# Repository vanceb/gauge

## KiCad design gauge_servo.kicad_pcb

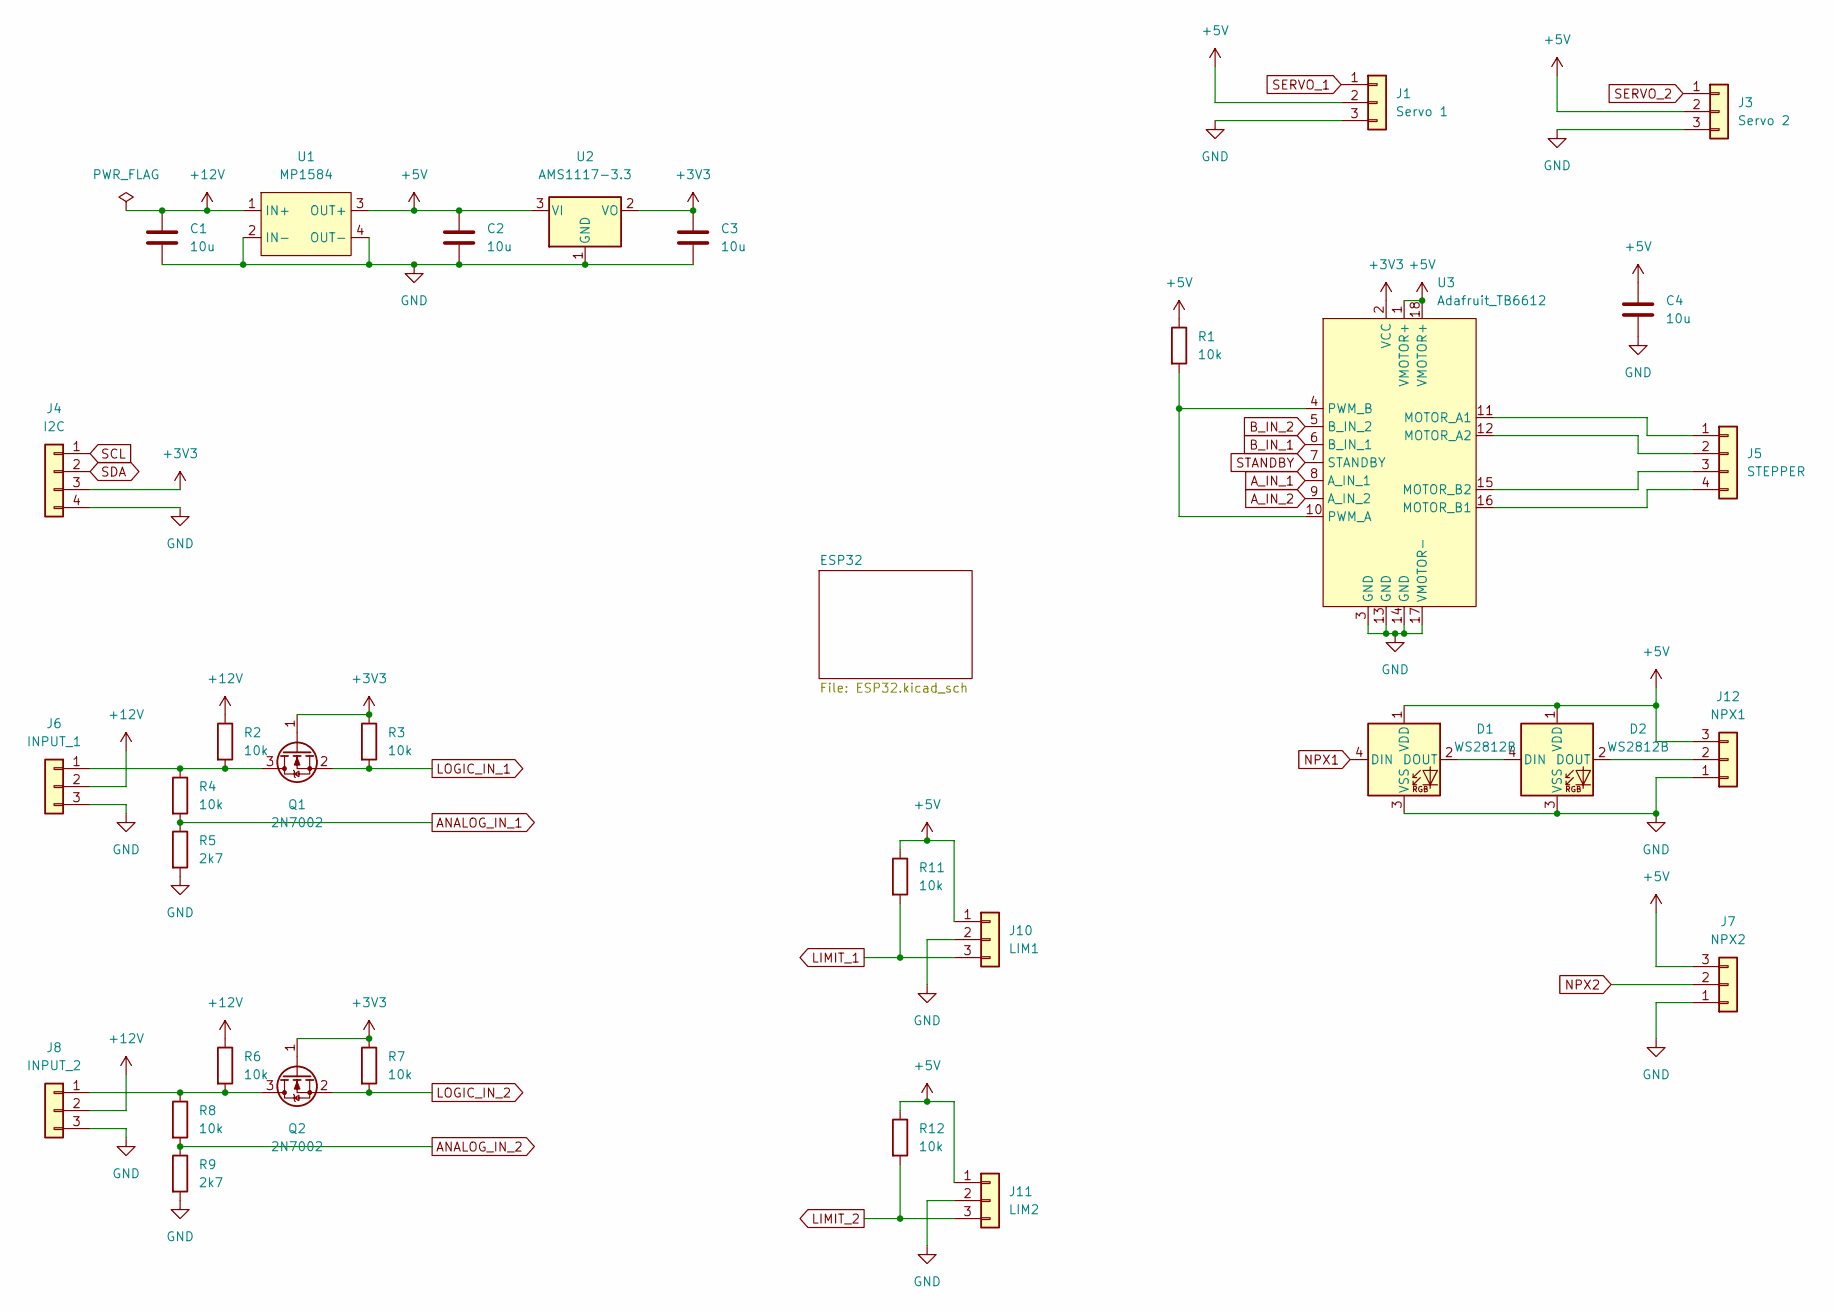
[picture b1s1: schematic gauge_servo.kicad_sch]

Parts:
C1, C2, C3, C4: 10u; C_1206_3216Metric; LCSC C13585
D1, D2: WS2812B; LED_WS2812B_PLCC4_5.0x5.0mm_P3.2mm
J1: Servo 1; PinHeader_1x03_P2.54mm_Vertical
J3: Servo 2; PinHeader_1x03_P2.54mm_Vertical
J4: I2C; PinHeader_1x04_P2.54mm_Vertical
J5: STEPPER; PinHeader_1x04_P2.54mm_Vertical
J6: INPUT_1; PinHeader_1x03_P2.54mm_Vertical
J7: NPX2; PinHeader_1x03_P2.54mm_Vertical
J8: INPUT_2; PinHeader_1x03_P2.54mm_Vertical
J10: LIM1; PinHeader_1x03_P2.54mm_Vertical
J11: LIM2; PinHeader_1x03_P2.54mm_Vertical
J12: NPX1; PinHeader_1x03_P2.54mm_Vertical
Q1, Q2: 2N7002; SOT-23; LCSC C8545
R1, R2, R3, R4, R6, R7, R8, R11, R12: 10k; R_0603_1608Metric; LCSC C25804
R5, R9: 2k7; R_0603_1608Metric; LCSC C13167
U1: MP1584
U2: AMS1117-3.3; SOT-223-3_TabPin2; LCSC C6186
U3: Adafruit_TB6612

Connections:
+3V3: C3.1, J4.3, Q1.1 (G), Q2.1 (G), R3.1, R7.1, U2.2 (VO), U3.2 (VCC); also elsewhere on the board
+5V: C2.1, C4.1, D1.1 (VDD), D2.1 (VDD), J1.2, J3.2, J7.3, J10.1, J11.1, J12.3, R1.1, R11.1, R12.1, U1.3 (OUT+), U2.3 (VI), U3.1 (VMOTOR+), U3.18 (VMOTOR+)
+12V: C1.1, J6.2, J8.2, R2.1, R6.1, U1.1 (IN+)
ANALOG_IN_1: R4.2, R5.1; also elsewhere on the board
ANALOG_IN_2: R8.2, R9.1; also elsewhere on the board
A_IN_1: U3.8 (A_IN_1); also elsewhere on the board
A_IN_2: U3.9 (A_IN_2); also elsewhere on the board
B_IN_1: U3.6 (B_IN_1); also elsewhere on the board
B_IN_2: U3.5 (B_IN_2); also elsewhere on the board
GND: C1.2, C2.2, C3.2, C4.2, D1.3 (VSS), D2.3 (VSS), J1.3, J3.3, J4.4, J6.3, J7.1, J8.3, J10.2, J11.2, J12.1, R5.2, R9.2, U1.2 (IN-), U1.4 (OUT-), U2.1 (GND), U3.3 (GND), U3.13 (GND), U3.14 (GND), U3.17 (VMOTOR-); also elsewhere on the board
LIMIT_1: J10.3, R11.2; also elsewhere on the board
LIMIT_2: J11.3, R12.2; also elsewhere on the board
LOGIC_IN_1: Q1.2 (S), R3.2; also elsewhere on the board
LOGIC_IN_2: Q2.2 (S), R7.2; also elsewhere on the board
NPX1: D1.4 (DIN); also elsewhere on the board
NPX2: J7.2; also elsewhere on the board
unnamed: D1.2 (DOUT), D2.4 (DIN)
unnamed: D2.2 (DOUT), J12.2
unnamed: J5.1, U3.11 (MOTOR_A1)
unnamed: J5.2, U3.12 (MOTOR_A2)
unnamed: J5.3, U3.15 (MOTOR_B2)
unnamed: J5.4, U3.16 (MOTOR_B1)
unnamed: J6.1, Q1.3 (D), R2.2, R4.1
unnamed: J8.1, Q2.3 (D), R6.2, R8.1
unnamed: R1.2, U3.4 (PWM_B), U3.10 (PWM_A)
SCL: J4.1; also elsewhere on the board
SDA: J4.2; also elsewhere on the board
SERVO_1: J1.1; also elsewhere on the board
SERVO_2: J3.1; also elsewhere on the board
STANDBY: U3.7 (STANDBY); also elsewhere on the board

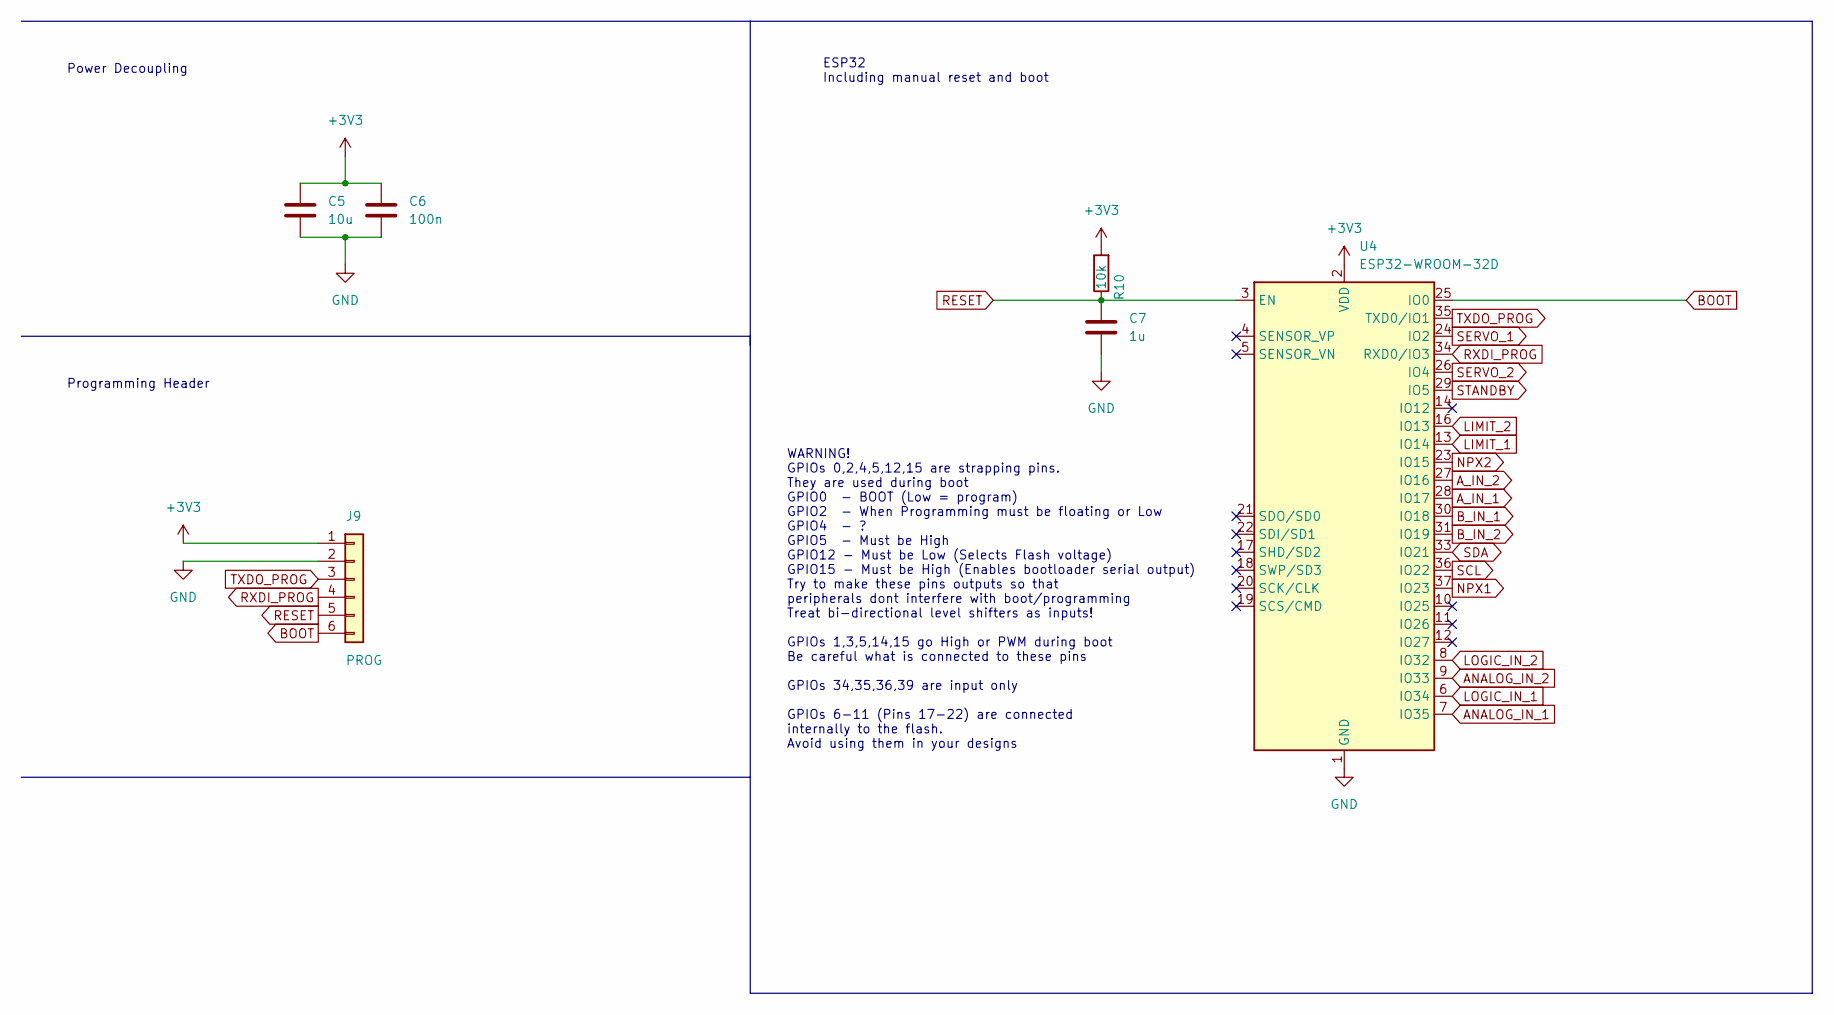
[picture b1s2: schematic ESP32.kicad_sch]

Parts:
C5: 10u; C_1206_3216Metric; LCSC C13585
C6: 100n; C_0603_1608Metric; LCSC C14663
C7: 1u; C_0603_1608Metric; LCSC C15849
J9: PROG; PinHeader_1x06_P2.54mm_Vertical
R10: 10k; R_0603_1608Metric_Pad0.98x0.95mm_HandSolder; LCSC C25804
U4: ESP32-WROOM-32D; ESP32-WROOM-32; LCSC C473012

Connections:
+3V3: C5.1, C6.1, J9.1, R10.2, U4.2 (VDD); also elsewhere on the board
ANALOG_IN_1: U4.7 (IO35); also elsewhere on the board
ANALOG_IN_2: U4.9 (IO33); also elsewhere on the board
A_IN_1: U4.28 (IO17); also elsewhere on the board
A_IN_2: U4.27 (IO16); also elsewhere on the board
BOOT: J9.6, U4.25 (IO0)
B_IN_1: U4.30 (IO18); also elsewhere on the board
B_IN_2: U4.31 (IO19); also elsewhere on the board
GND: C5.2, C6.2, C7.2, J9.2, U4.1 (GND), U4.15 (GND), U4.38 (GND), U4.39 (GND); also elsewhere on the board
LIMIT_1: U4.13 (IO14); also elsewhere on the board
LIMIT_2: U4.16 (IO13); also elsewhere on the board
LOGIC_IN_1: U4.6 (IO34); also elsewhere on the board
LOGIC_IN_2: U4.8 (IO32); also elsewhere on the board
NPX1: U4.37 (IO23); also elsewhere on the board
NPX2: U4.23 (IO15); also elsewhere on the board
RESET: C7.1, J9.5, R10.1, U4.3 (EN)
RXDI_PROG: J9.4, U4.34 (RXD0/IO3)
SCL: U4.36 (IO22); also elsewhere on the board
SDA: U4.33 (IO21); also elsewhere on the board
SERVO_1: U4.24 (IO2); also elsewhere on the board
SERVO_2: U4.26 (IO4); also elsewhere on the board
STANDBY: U4.29 (IO5); also elsewhere on the board
TXDO_PROG: J9.3, U4.35 (TXD0/IO1)

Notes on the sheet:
ESP32 Including manual reset and boot
Programming Header
WARNING! GPIOs 0,2,4,5,12,15 are strapping pins. They are used during boot GPIO0 - BOOT (Low = program) GPIO2 - When Programming must be floating or Low GPIO4 - ? GPIO5 - Must be High GPIO12 - Must be Low (Selects Flash voltage) GPIO15 - Must be High (Enables bootloader serial output) Try to make t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
Power Decoupling

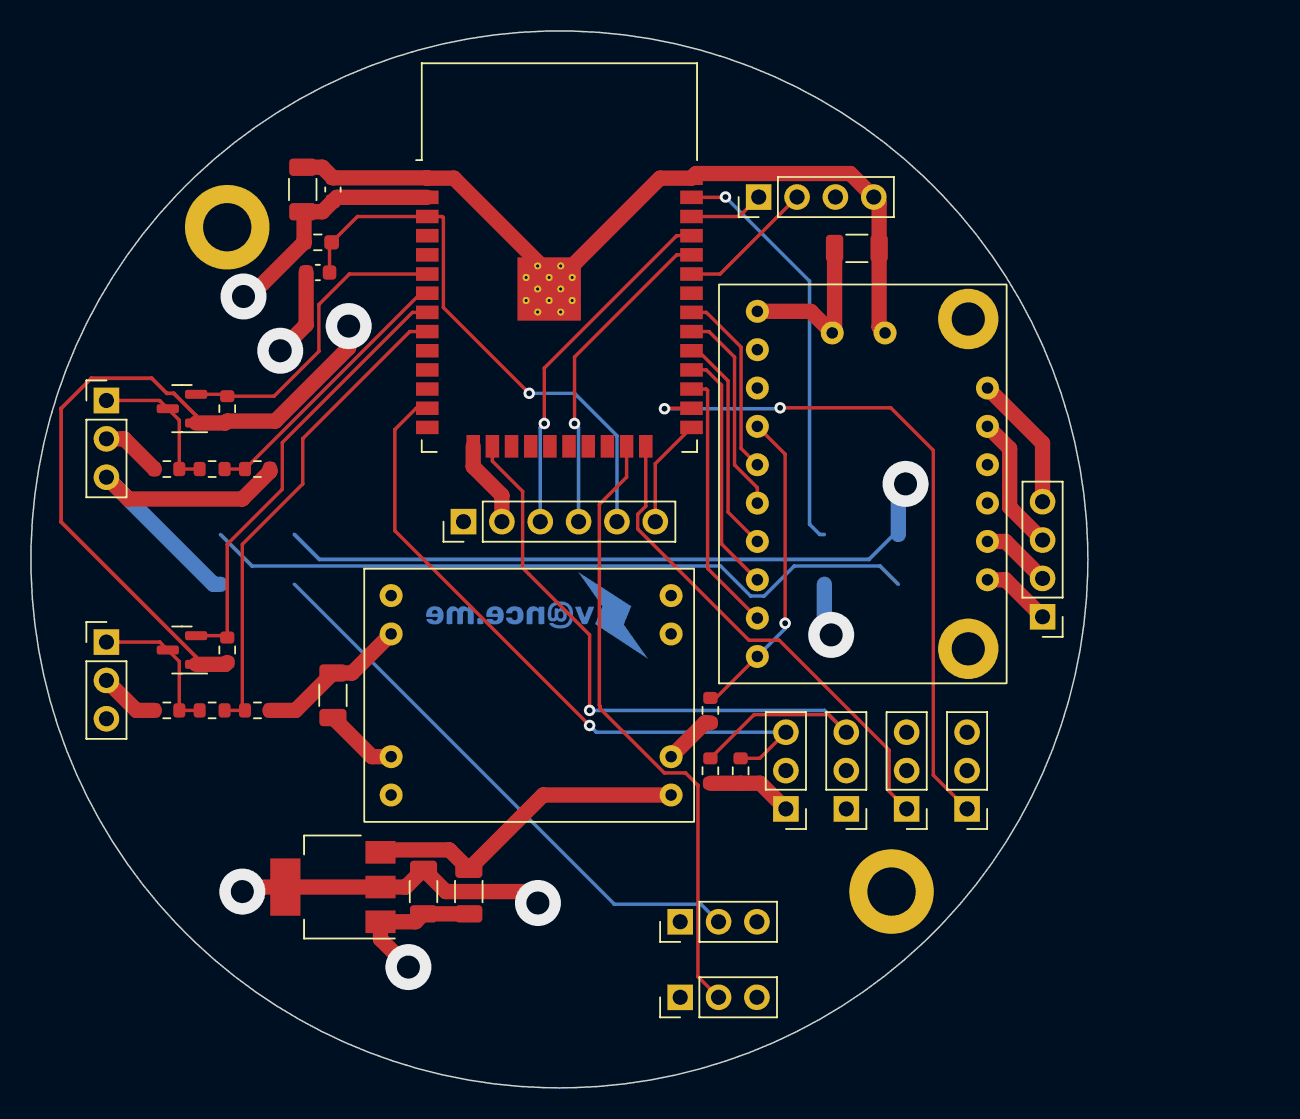
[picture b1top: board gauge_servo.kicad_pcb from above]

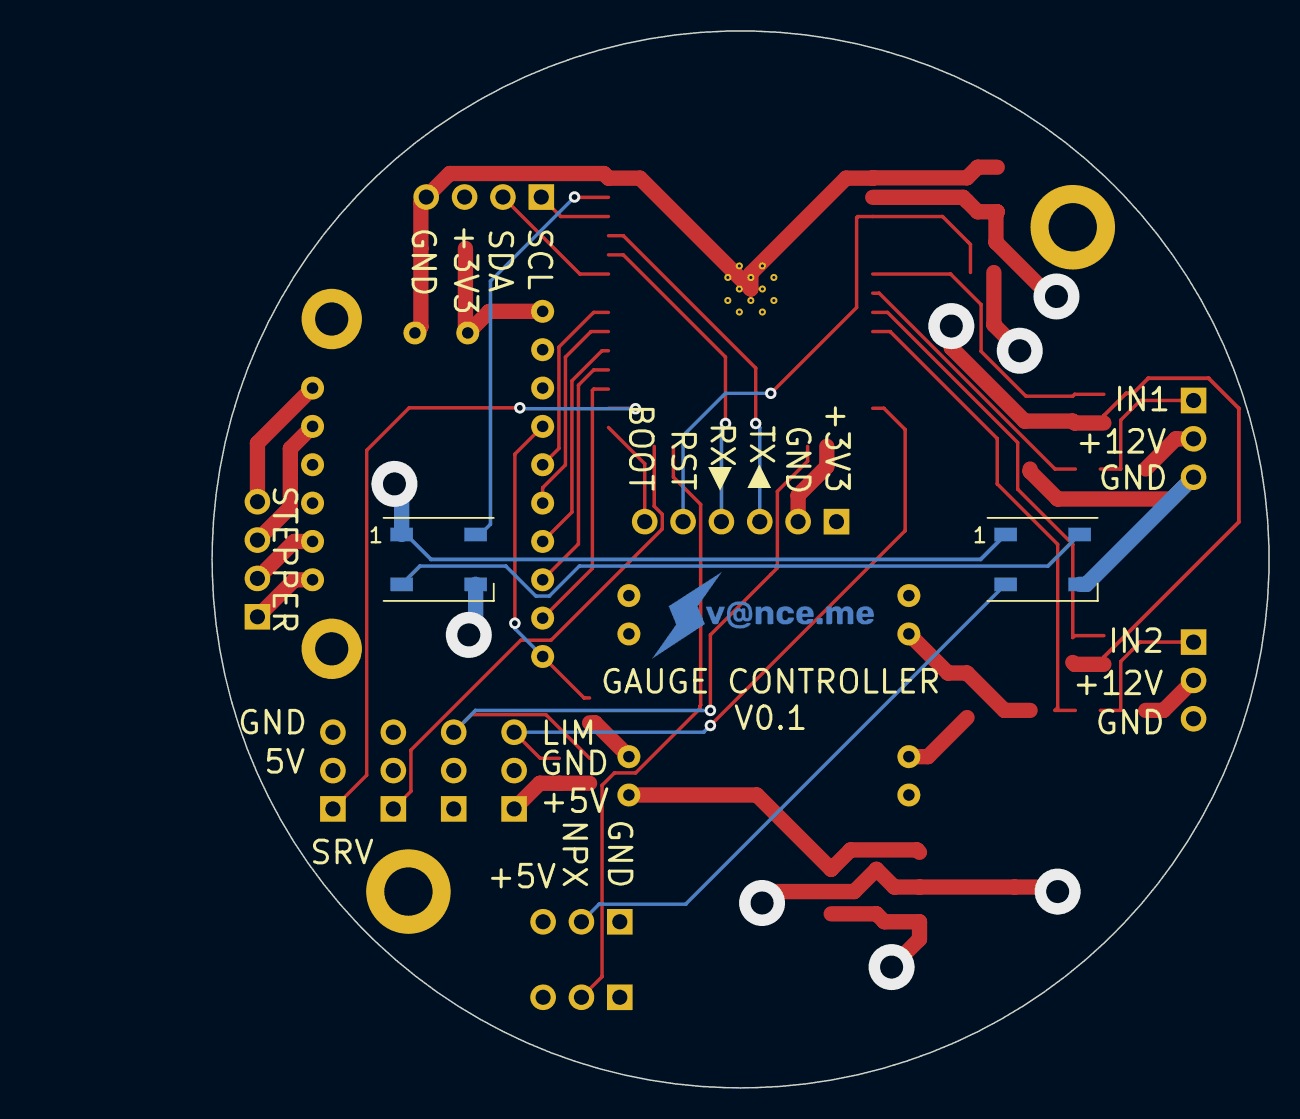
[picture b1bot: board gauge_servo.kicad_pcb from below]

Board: 4 copper layers, 82.0 x 70.0 mm, 38 parts (2 on the bottom side), 34 nets.

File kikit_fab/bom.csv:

Comment,Designator,Footprint,LCSC
10u,"C1,C2,C3,C4,C5",Capacitor_SMD:C_1206_3216Metric,C13585
100n,C6,Capacitor_SMD:C_0603_1608Metric,C14663
1u,C7,Capacitor_SMD:C_0603_1608Metric,C15849
WS2812B,"D1,D2",LED_SMD:LED_WS2812B_PLCC4_5.0x5.0mm_P3.2mm,
Servo 1,J1,Connector_PinHeader_2.54mm:PinHeader_1x03_P2.54mm_Vertical,
Servo 2,J3,Connector_PinHeader_2.54mm:PinHeader_1x03_P2.54mm_Vertical,
I2C,J4,Connector_PinHeader_2.54mm:PinHeader_1x04_P2.54mm_Vertical,
STEPPER,J5,Connector_PinHeader_2.54mm:PinHeader_1x04_P2.54mm_Vertical,
INPUT_1,J6,Connector_PinHeader_2.54mm:PinHeader_1x03_P2.54mm_Vertical,
NPX2,J7,Connector_PinHeader_2.54mm:PinHeader_1x03_P2.54mm_Vertical,
INPUT_2,J8,Connector_PinHeader_2.54mm:PinHeader_1x03_P2.54mm_Vertical,
PROG,J9,Connector_PinHeader_2.54mm:PinHeader_1x06_P2.54mm_Vertical,
LIM1,J10,Connector_PinHeader_2.54mm:PinHeader_1x03_P2.54mm_Vertical,
LIM2,J11,Connector_PinHeader_2.54mm:PinHeader_1x03_P2.54mm_Vertical,
NPX1,J12,Connector_PinHeader_2.54mm:PinHeader_1x03_P2.54mm_Vertical,
2N7002,"Q1,Q2",Package_TO_SOT_SMD:SOT-23,C8545
10k,"R1,R2,R3,R4,R6,R7,R8,R11,R12",Resistor_SMD:R_0603_1608Metric,C25804
2k7,"R5,R9",Resistor_SMD:R_0603_1608Metric,C13167
10k,R10,Resistor_SMD:R_0603_1608Metric_Pad0.98x0.95mm_HandSolder,C25804
MP1584,U1,MP1584:MP1584,
AMS1117-3.3,U2,Package_TO_SOT_SMD:SOT-223-3_TabPin2,C6186
Adafruit_TB6612,U3,Adafruit_TB6612:Adafruit_TB6612,
ESP32-WROOM-32D,U4,RF_Module:ESP32-WROOM-32,C473012

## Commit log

2022-12-19 v0.1 production files
2022-12-30 Added .gitignore to remove backups from the archive
2022-12-30 Fixed pinout error or Adafruit TB6612 custom component that caused short between 5V and gnd
2022-12-30 Moved LIMIT1 signal away from IO12 where the pullup was stopping the ESP from booting
